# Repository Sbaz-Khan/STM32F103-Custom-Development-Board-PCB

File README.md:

# STM32F103 Custom Development Board PCB

A custom two-layer development board built around the **STM32F103C8T6** microcontroller using **KiCad**.

This project was completed as a hands-on PCB design exercise based on **Phil's Lab's STM32 PCB tutorial**, with the goal of learning and practicing the complete workflow from **schematic capture to PCB layout and manufacturing-file generation**.

---

## Final PCB

The completed board integrates power regulation, clock circuitry, USB, programming/debugging interfaces, serial communication interfaces, analog power filtering, and a two-layer PCB layout with a dedicated ground plane.

---

## Main Features

- **STM32F103C8T6** ARM Cortex-M3 microcontroller
- **USB Micro-B** power and data interface
- **AMS1117-3.3** linear voltage regulator
- 5 V USB VBUS to regulated **3.3 V**
- MCU decoupling and bulk capacitance
- Filtered **VDDA analog supply**
- **16 MHz external crystal oscillator**
- **BOOT0** mode-selection switch
- **NRST** reset filtering
- **SWD** programming/debugging header
- **USART/UART** communication header
- **I²C** communication header with pull-up resistors
- USB **D+ / D− differential-pair routing**
- Power-status LED
- Four M2 mounting holes
- Two-layer PCB with **B.Cu GND plane**
- ERC and DRC verification
- BOM, Gerber, drill, and position-file generation

---

## System Architecture

```text
                     USB Micro-B
                         │
          ┌──────────────┴──────────────┐
          │                             │
       USB D+/D−                     VBUS 5 V
          │                             │
          ▼                             ▼
       STM32F103                  AMS1117-3.3
          │                             │
          │                             ▼
          │                           3.3 V
          │                             │
     ┌────┼───────────────┬─────────────┼─────────────┐
     │    │               │             │             │
     ▼    ▼               ▼             ▼             ▼
    SWD  USART           I²C        STM32 VDD      VDDA Filter
                                                    │
                                             Ferrite Bead +
                                               Capacitors
                                                    │
                                                    ▼
                                                STM32 VDDA
```

---

## Schematic Design

The schematic was organized into several functional blocks:

- STM32F103C8T6 microcontroller
- 3.3 V power regulation
- VDD decoupling
- VDDA filtering
- NRST reset circuit
- BOOT0 selection
- 16 MHz crystal oscillator
- USB interface
- SWD interface
- USART/UART interface
- I²C interface
- power indicator LED
- mounting holes

The design uses an **AMS1117-3.3 linear regulator** to convert USB VBUS to the 3.3 V rail required by the STM32 and external interfaces.

A ferrite-bead filtering network provides a cleaner 3.3 V analog supply for the STM32 VDDA pin.

---

## Communication Interfaces

### SWD

The SWD header provides programming and debugging access through:

- SWDIO
- SWCLK
- 3.3 V reference
- GND

It is intended for use with an **ST-Link programmer/debugger**.

### USART / UART

A 1×4 header exposes:

- TX
- RX
- 3.3 V
- GND

This provides a simple serial communication interface for external devices.

### I²C

A separate 1×4 header exposes:

- SCL
- SDA
- 3.3 V
- GND

Pull-up resistors are included on SCL and SDA as required by the I²C bus.

### USB

The STM32's native USB interface is connected through:

- PA11 → USB D−
- PA12 → USB D+

The pair was routed together as a differential pair on the PCB.

---

## PCB Layout

The PCB was implemented as a **two-layer board**.

### F.Cu

Used primarily for:

- signal routing
- power routing
- component interconnections

### B.Cu

Used primarily as a continuous **GND plane**.

Ground vias connect front-side ground connections to the bottom ground plane.

---

## Placement and Routing

Important layout decisions included:

- decoupling capacitors placed close to STM32 power pins
- crystal placed close to the oscillator pins
- USB connector positioned at the board edge
- regulator positioned near the USB power input
- communication headers positioned for easy access
- mounting holes placed near the board corners
- B.Cu kept largely continuous as a ground plane

Two primary trace widths were used:

- **0.3 mm** for most signals and fine-pitch MCU connections
- **0.5 mm** for wider 3.3 V power distribution

USB D+ and D− were routed as a differential pair.

---

## Grounding Strategy

The bottom copper layer was filled with a **GND copper zone**.

This provides:

- a low-impedance ground path
- simpler ground routing
- improved signal return paths
- improved noise performance

GND vias were used where SMD ground connections needed to connect to the B.Cu ground plane.

---

## Design Verification

### ERC

KiCad's **Electrical Rules Checker** was used during schematic development to identify electrical-rule issues and unintentionally unconnected pins.

### DRC

KiCad's **Design Rules Checker** was used after layout and routing to verify:

- connectivity
- clearances
- trace widths
- via dimensions
- board-edge spacing
- unconnected items

Final result:

- **0 DRC errors**
- **0 unconnected items**

One understood warning remained because the BOOT0 switch footprint had been locally modified compared with the original KiCad library footprint.

---

## Bill of Materials

A BOM was generated from KiCad containing:

- reference designators
- quantities
- component values
- footprints
- datasheets

Additional fields were added for:

- Manufacturer
- Manufacturer Part Number (MPN)

These fields can be populated with the exact components selected for fabrication and assembly.

---

## Manufacturing Outputs

The project was taken through the manufacturing-output stage.

Generated files include:

- front and back copper Gerbers
- solder-mask layers
- silkscreen layers
- Edge.Cuts
- drill files
- BOM
- component position / pick-and-place files

The Gerbers were reviewed using KiCad's Gerber Viewer before finalizing the output files.

---

## Design Workflow

```text
Study STM32 Requirements
          │
          ▼
    Create Schematic
          │
          ▼
         ERC
          │
          ▼
   Assign Footprints
          │
          ▼
   Place Components
          │
          ▼
 Route Signals + Power
          │
          ▼
 Add GND Vias + Plane
          │
          ▼
     Add Silkscreen
          │
          ▼
         DRC
          │
          ▼
     3D Inspection
          │
          ▼
       Generate BOM
          │
          ▼
Gerbers + Drill + Position Files
```

---

## Repository Structure

```text
STM32F103-Custom-Development-Board-PCB/
│
├── README.md
│
├── hardware/
│   └── KiCad schematic, PCB, project, and related design files
│
├── manufacturing/
│   └── Gerbers, drill files, BOM, and position files
│
├── media/
│   ├── Schematic.png
│   ├── Layout.png
│   ├── 3D-Preview.png
│   ├── BOM.png
│   └── Gerber.png
│
└── documentation/
    └── Detailed technical documentation and design notes
```

---

## Key Skills Practiced

- PCB Design
- KiCad
- STM32 hardware design
- Schematic capture
- PCB layout and routing
- Power distribution
- Ground-plane design
- Differential-pair routing
- Component footprint selection
- ERC / DRC
- BOM generation
- Manufacturing-file preparation
- Datasheet interpretation
- STM32CubeIDE / CubeMX

---

## Project Outcome

The project resulted in a complete two-layer STM32 development-board design containing:

- STM32F103C8T6
- regulated 3.3 V power
- filtered analog supply
- external 16 MHz oscillator
- USB connectivity
- SWD programming/debugging
- USART
- I²C
- BOOT0 selection
- reset circuitry
- power indication
- mounting holes
- front-layer routing
- bottom-layer ground plane
- manufacturing outputs

The design was completed through the **PCB verification and manufacturing-preparation stage**.

---

## Detailed Documentation

A much more detailed explanation of the project is available in the [`documentation`](documentation/) folder.

The technical document covers topics such as:

- decoupling and bulk capacitors
- ferrite-bead filtering
- VDD / VDDA
- NRST
- BOOT0
- crystal oscillator operation
- USB D+ pull-up
- USB differential signalling
- SWD
- UART
- I²C and open-drain signalling
- vias and ground planes
- footprints and 3D models
- ERC and DRC
- BOM preparation
- Gerbers and manufacturing outputs

This README is intended as a concise technical overview, while the documentation folder contains the full theory and design notes.

---

## Attribution

This project was built as a **hands-on PCB design exercise based on Phil's Lab's STM32 PCB tutorial**, with the goal of understanding and practicing the complete schematic-to-manufacturing workflow.

The project is presented as a learning implementation rather than as an original reference-board architecture.

---

## Tools

- **KiCad** — schematic capture, PCB layout, ERC/DRC, 3D inspection, Gerber generation
- **STM32CubeIDE / CubeMX** — STM32 peripheral and pin configuration
- **STM32F103C8T6** — target microcontroller
- **GitHub** — project documentation and design-file management

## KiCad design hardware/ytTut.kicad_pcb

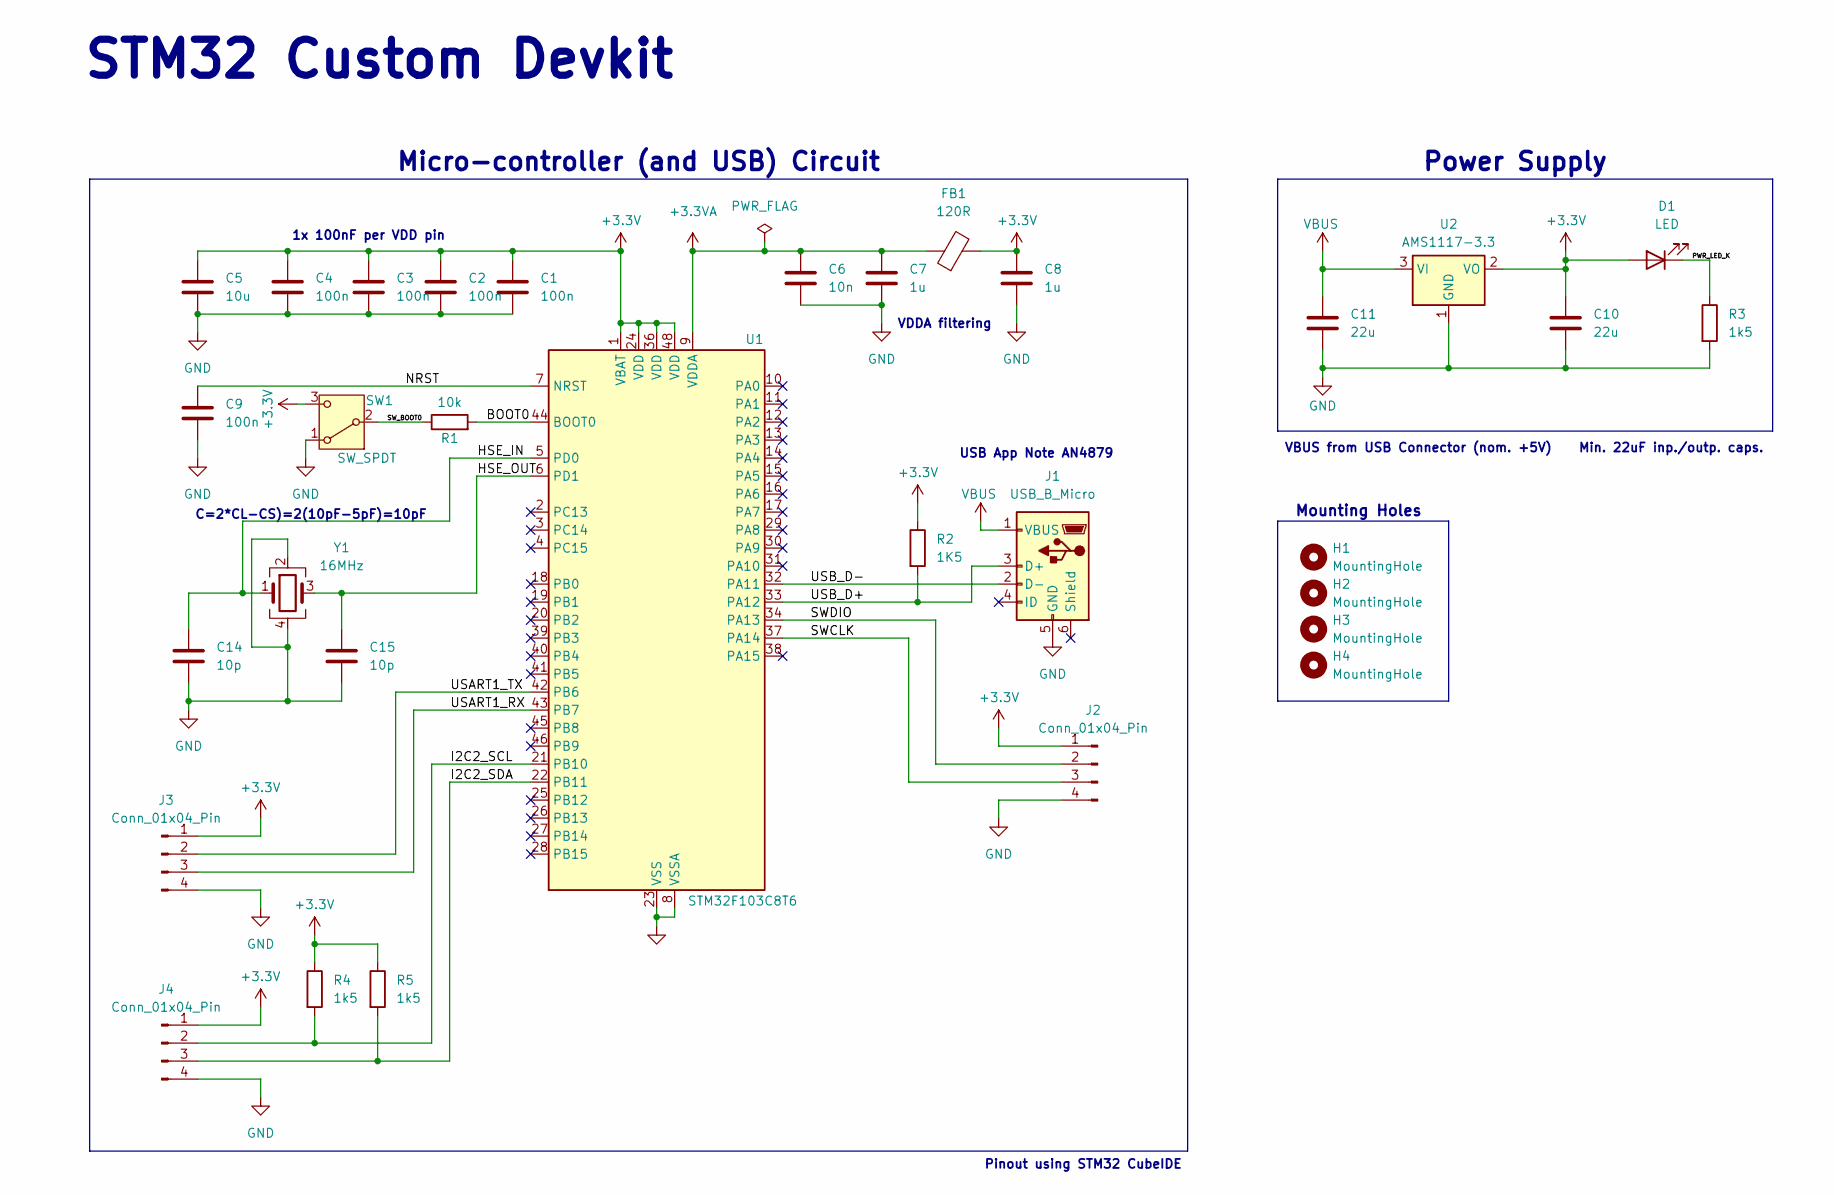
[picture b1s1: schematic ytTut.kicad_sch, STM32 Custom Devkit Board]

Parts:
C1, C2, C3, C4, C9: 100n; C_0402_1005Metric
C5: 10u; C_0603_1608Metric
C6: 10n; C_0402_1005Metric
C7, C8: 1u; C_0402_1005Metric
C10, C11: 22u; C_0805_2012Metric
C14, C15: 10p; C_0402_1005Metric
D1: LED; LED_0603_1608Metric
FB1: 120R; L_0603_1608Metric
H1, H2, H3, H4: MountingHole; MountingHole_2.2mm_M2
J1: USB_B_Micro; USB_Micro-B_Wuerth_629105150521
J2, J3, J4: Conn_01x04_Pin; PinHeader_1x04_P2.54mm_Vertical
R1: 10k; R_0402_1005Metric
R2: 1K5; R_0402_1005Metric
R3, R4, R5: 1k5; R_0402_1005Metric
SW1: SW_SPDT; SW_SPDT_PCM12
U1: STM32F103C8T6; LQFP-48_7x7mm_P0.5mm
U2: AMS1117-3.3; SOT-223-3_TabPin2
Y1: 16MHz; Crystal_SMD_3225-4Pin_3.2x2.5mm

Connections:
+3.3V: C1.1, C2.1, C3.1, C4.1, C5.1, C8.1, C10.1, D1.2 (A), FB1.2, J2.1, J3.1, J4.1, R2.1, R4.1, R5.1, SW1.3 (C), U1.1 (VBAT), U1.24 (VDD), U1.36 (VDD), U1.48 (VDD), U2.2 (VO)
+3.3VA: C6.1, C7.1, FB1.1, U1.9 (VDDA)
/BOOT0: R1.2, U1.44 (BOOT0)
/HSE_IN: C14.1, U1.5 (PD0), Y1.1
/HSE_OUT: C15.1, U1.6 (PD1), Y1.3
/I2C2_SCL: J4.2, R4.2, U1.21 (PB10)
/I2C2_SDA: J4.3, R5.2, U1.22 (PB11)
/NRST: C9.1, U1.7 (NRST)
/PWR_LED_K: D1.1 (K), R3.1
/SWCLK: J2.3, U1.37 (PA14)
/SWDIO: J2.2, U1.34 (PA13)
/SW_BOOT0: R1.1, SW1.2 (B)
/USART1_RX: J3.3, U1.43 (PB7)
/USART1_TX: J3.2, U1.42 (PB6)
/USB_D+: J1.3 (D+), R2.2, U1.33 (PA12)
/USB_D-: J1.2 (D-), U1.32 (PA11)
GND: C1.2, C2.2, C3.2, C4.2, C5.2, C6.2, C7.2, C8.2, C9.2, C10.2, C11.2, C14.2, C15.2, J1.5 (GND), J2.4, J3.4, J4.4, R3.2, SW1.1 (A), U1.8 (VSSA), U1.23 (VSS), U1.35 (VSS), U1.47 (VSS), U2.1 (GND), Y1.2, Y1.4
VBUS: C11.1, J1.1 (VBUS), U2.3 (VI)

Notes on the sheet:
Micro-controller (and USB) Circuit
Mounting Holes
C=2*CL​−CS​)=2(10pF−5pF)=10pF
Power Supply
1x 100nF per VDD pin
USB App Note AN4879
VBUS from USB Connector (nom. +5V) Min. 22uF inp./outp. caps.
VDDA filtering
STM32 Custom Devkit
Pinout using STM32 CubeIDE

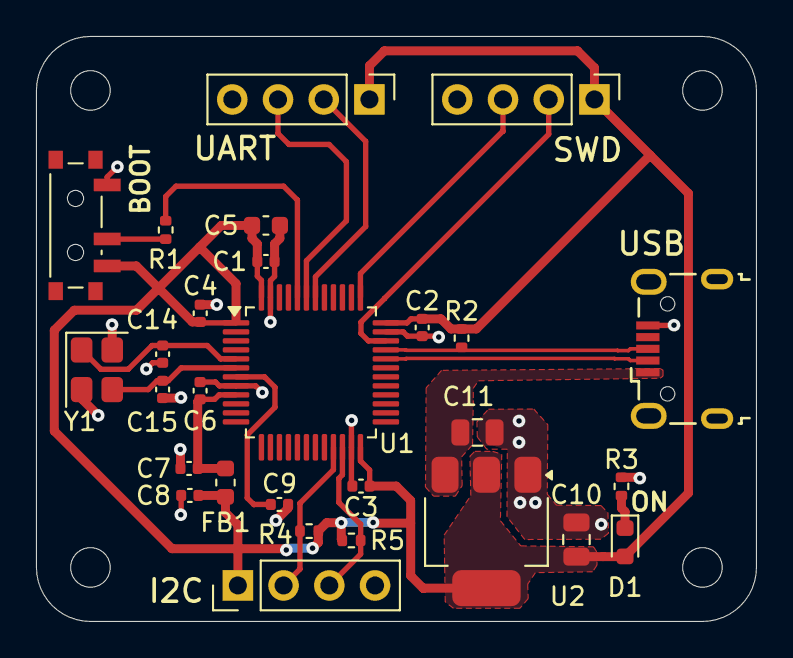
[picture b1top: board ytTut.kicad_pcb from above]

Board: 2 copper layers, 40.0 x 32.5 mm, 32 parts (0 on the bottom side), 18 nets.
